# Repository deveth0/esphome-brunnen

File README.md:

# esphome-brunnen

Repository with all required stuff to build an esphome node that monitors the waterlevel and temperature of a well or cistern. It does not require any power connection as it's using a solar panel and some batteries. 

## PCB

You can find a KiCad Model in this repository. The PCB can be mounted (aka glued) to the battery case of the [Waveshare Solar Power Manager D](https://www.waveshare.com/solar-power-manager-d.htm). Using the spacers that come with the Solar board, you can mount it to the PCB. 

### Parts

| Number | Component | Position on PCB|
| --------- | ------ | -------- |
| 1 | Solar Panel, 6-24V, see below | | |
| 1 | [Waveshare Solar Power Manager D](https://www.waveshare.com/solar-power-manager-d.htm)|
| 3 | 18650 Li-ion batteries|
| 1 | MT3608 step up module | | |
| 1 | D1 Mini ESP32 with headers ||
| 1 | TL-136 Sensor, 4-20mA, 24V ||
| 1 | DS18B20 Sensor, waterproof ||
| 1 | JST-XH 2 Pin cable | |
| 2 | JST-XH 3 Pin cable | |
| 1 | JST-XH 4 Pin cable | |
| 1 | BC547 | Q1 |
| 1 | BC557 | Q2 |
| 1 | tantalum capacitor 35V  1uF | C1 |
| 1 | JST-XH 2 Pin Header | J3 |
| 2 | JST-XH 3 Pin Header | J1, J4 |
| 1 | JST-XH 4 Pin Header | J2 |
| 1 | DS18B20 Sensor, TO-92 package | U2 |
| 1 | Resistor, 4.7k | R1 |
| 1 | Resistor, 33k | R2 |
| 1 | Resistor, 100k | R3 |
| 2 | Resistor, 150k | R4, R5 (see note below) |
| 2 | Resistor, 1k | R6, R9 |
| 1 | Resistor, 150 | R7 |
| 1 | Resistor, 27k | R8 |
| 1 | Resistor, 10k | R10 |

### D1 Mini ESP32

Before adding the D1 Mini to your PCB (i highly recommend using headers), you need to install the software to the board. All subsequent updates can be done using OTA but the first installation requires an USB connection.

> [!CAUTION]
> DO NEVER CONNECT YOUR D1 BOARD VIA USB WHEN IT'S MOUNTED ON THE PCB

### Solar Panel

You can use any solar panel that provides between 6-24V. Choose wattage according to the placement of your panel. 

The resistors `R4` and `R5` are used to split the voltage of the solar panel into a range, that can be measured with an ESP32 gpio pin (max 3.3V). By using equally sized resistors, the voltage is cut by half, so this is fine for 6V panels.
Change the resistors to the following values, when using other panels, also change the multiply factor of the `solar_voltage` sensor in `brunnen.yaml`.

> [!WARNING]
> Some solar panels provide a slightly higher voltage than specified (e.g. 14V instead of 12V). To prevent any damage on the GPIO pin, use the resistor and multiply value of the next higher rated panel if you are not sure. This reduces the accuracy of the measured voltage a bit, but might save your D1.

| Panel | R4 | R5 | max V @ GPIO | `multiply` |
| ----- | -- | -- | ------|---------- |
| 6V | 150k | 150k| 3V |`multiply: 2`|
| 12V | 150k | 47k| 2.86|`multiply: 4.2`|
| 18V | 150k | 33k| 3.25V|`multiply: 5.5`|
| 24V | 150k | 22k| 3.07V |`multiply: 7.8`|

### MT3608 Step up Module

The pressure sensor requires 24V which are generated by a step up module. The module is disabled when the ESP32 is in deepsleep using a BC547 transistor to reduce the power consumption.

Before adding the MT3608 to your circuit, you need to measure and change the output voltage to 24V, use a multimeter for that task.

### Assembly

* Solder the 2 Pin JST-XH cable to your pressure sensor
* Solder one 3 Pin JST-XH cable to your waterproof DS18B20 sensor
* Solder one 1 Pin JST-XH cable to your MT3608 step-up
    * VIN
    * GND
    * VOUT
* Attach one 4 Pin JST-XH cable to your Waveshare Board:
    * GND
    * 5V
    * BAT+ (use the free terminal)
    * SOL+ (add cable together with solar panel to terminal)
* Add solar panel to Waveshare Board
* Attach batteries
* Solder all remaining parts to the PCB
* Check parts once again
* Connect J2 to JST-XH cable coming from Waveshare Board, your ESP32 should power up now
* Connect all remaining JST-XH cables
    * J1 - waterproof DS18B20
    * J3 - Pressure sensor
    * J4 - MT3608 Module

You should now see some sensor readings and can head over to the calibration of your pressure sensor. 

Note: to make the connections a bit more sturdy, you can also remove the terminals and solder all cables to the Waveshare Board

## Installation

### secrets.yaml

Create a `secrets.yaml` file which contains your WiFi-credentials:

```
wifi_ssid: "YOUR_SSID"
wifi_password: "YOUR_PASSWORD"
```

### Initial upload to ESP32

Attach your D1 Mini using USB to your computer, find out the correct COM port and run:

```
esphome run --device COM4 .\brunnen.yaml
```

The ESP32 should then reboot and connect to your wifi, note down it's IP.

> [!CAUTION]
> DO NEVER CONNECT YOUR D1 BOARD VIA USB WHEN IT'S MOUNTED TO THE PCB

### OTA Updates

When the initial upload is done, you can update your ESP32 using OTA updates. This does not require you to remove the board from the PCB. 

```
esphome run --device 10.0.50.132 .\brunnen.yaml
```

### D18B20 Sensors

Each of the D18B20 temperature sensors has a unique address that needs to be configured. Esphome logs all available devices when starting, you just need to figure out, which sensor is for the case and which one for water. 

```
[20:37:31][C][gpio.one_wire:020]: GPIO 1-wire bus:
[20:37:31][C][gpio.one_wire:021]:   Pin: GPIO5
[20:37:31][C][gpio.one_wire:080]:   Found devices:
[20:37:31][C][gpio.one_wire:082]:     0x5d4a131c35646128 (DS18B20)
[20:37:31][C][gpio.one_wire:082]:     0x8f00000e7dbdd128 (DS18B20)
```

### Pressure Sensor calibration

The pressure sensor gives around 4-20mA when submerged into water. Although this gives us a rough estimation, I recommend to calibrate the sensor with some known values. 

Use the log output to determine the values read by your ESP32, this is what we are looking for:

```
'Wasserstand Voltage': Sending state 0.27872 V with 2 decimals of accuracy
```

First note down the voltage when the sensor is not in water (basically 0cm). Then add as many data points as seem reasonable (e.g. one per meter).

When submerging the sensor, give it a minute or two so the value stabilizes.

Now update the mapping table to reflect your measurements
```
      - calibrate_linear:
            - 0.28 -> 0.0 # 0cm
            - 0.60 -> 1.2 # 120cm
            - 0.75 -> 2.2 # 220cm
            - 0.91 -> 3.2 # 320cm
            - 1.32 -> 4.2 # 420cm
```

## Home Assistant Integration 

Finally you can add the Board to your Home Assistant setup and configure a switch that enables/disables deep-sleep.

`Settings` > `Devices & Services` > `Add integration` > `esphome` > `Enter IP of your node`

### Deep Sleep Helper

By default the ESP32 board does not go to deep sleep. To allow OTA updates, a toggle in Home Assistant is used, that enables / disables sleep. As soon as the board wakes up, it checks if the toggle is enabled and only if so will sleep again. 

If you ever want to do an OTA update and your ESP32 is sleeping, disable the toggle, wait until it wakes up for the next time and you can proceed.

Create the toggle in Home Assistant:

`Settings` > `Devices & Services` > `Helpers` > `Create Helper` > `Toggle` 

Name the Helper `Enable ESPHome Deepsleep` (it's important that the id of the new helper matches the one configured in `brunnen.yaml`).

# Acknowledgement

* Thanks to [r0oland](https://github.com/r0oland) for the [ESP32 mini KiCad Library](https://github.com/r0oland/ESP32_mini_KiCad_Library)
* Thanks to [tathamoodie](https://github.com/tathamoddie) for his [blogpost]( https://tatham.blog/2021/02/06/esphome-batteries-deep-sleep-and-over-the-air-updates/) about deep sleep

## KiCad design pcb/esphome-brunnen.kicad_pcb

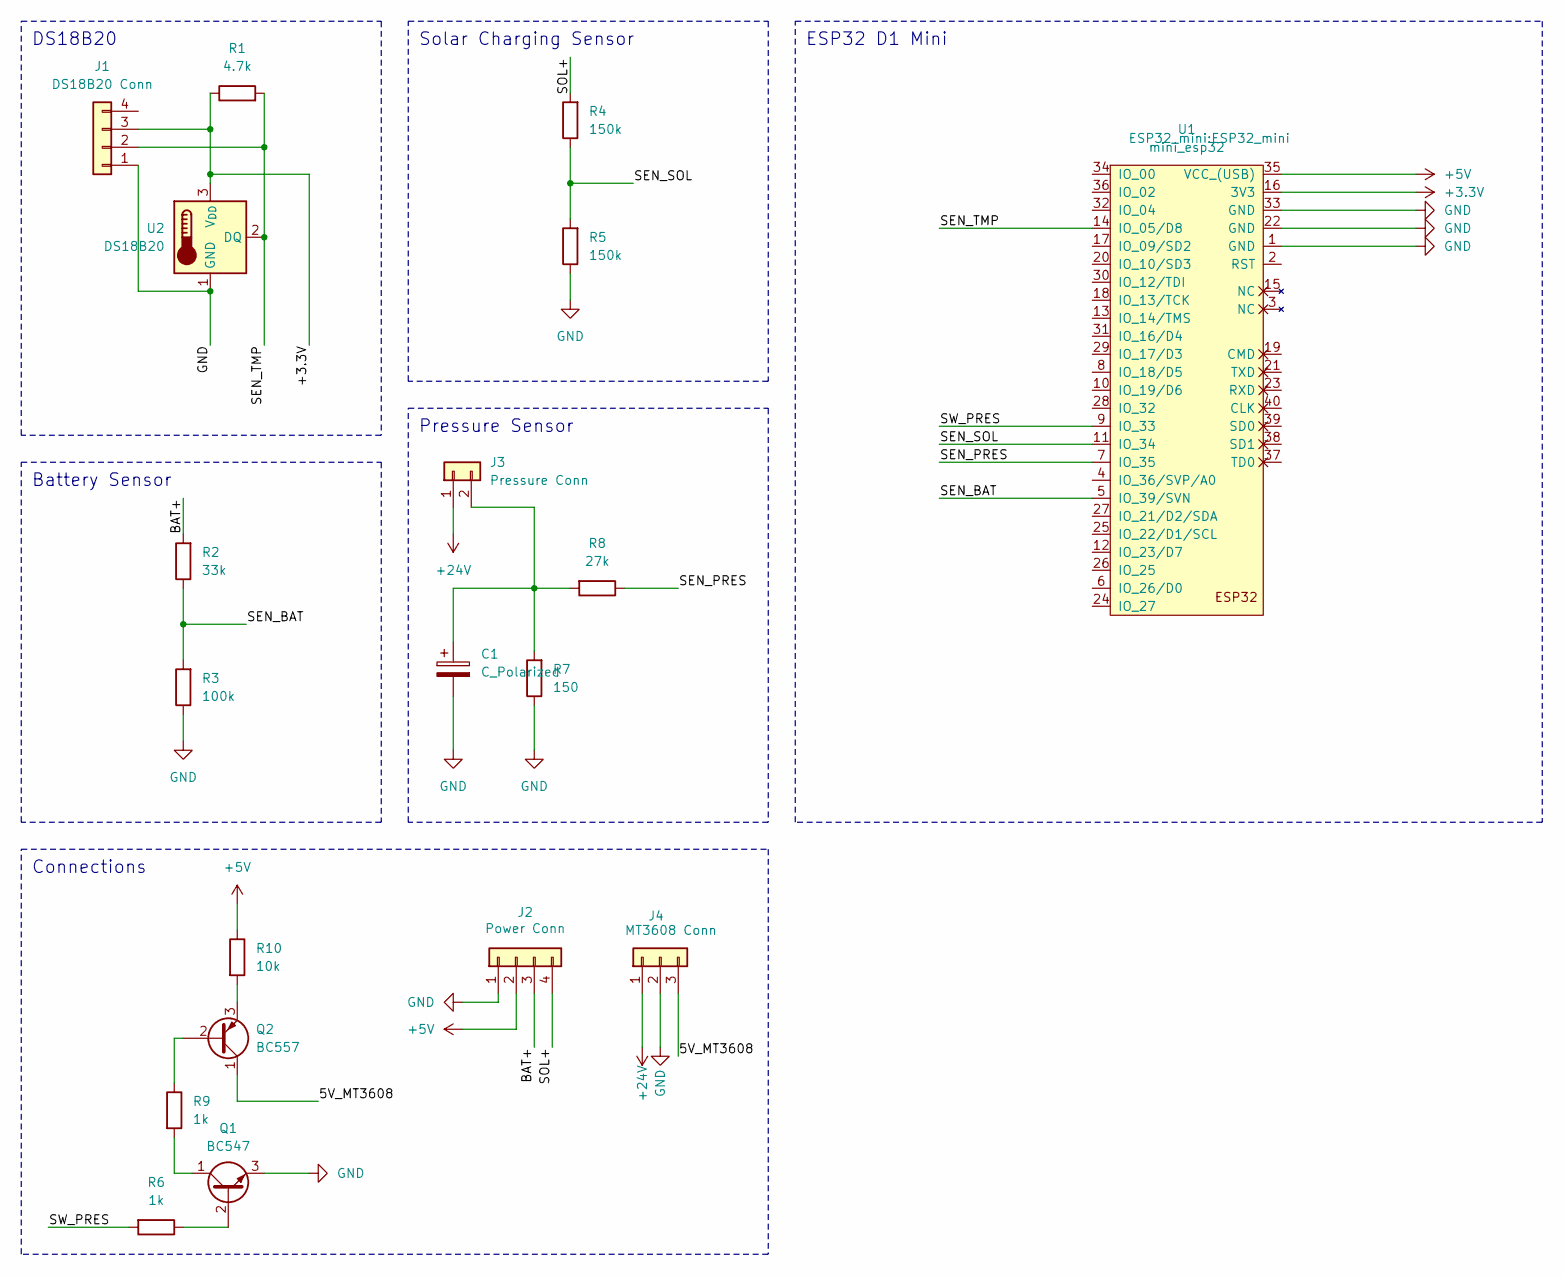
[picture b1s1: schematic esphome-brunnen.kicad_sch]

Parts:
C1: C_Polarized; CP_Radial_Tantal_D4.5mm_P2.50mm
J1: DS18B20 Conn; JST_XH_B3B-XH-A_1x03_P2.50mm_Vertical
J2: Power Conn; JST_XH_B4B-XH-A_1x04_P2.50mm_Vertical
J3: Pressure Conn; JST_XH_B2B-XH-A_1x02_P2.50mm_Vertical
J4: MT3608 Conn; JST_XH_B3B-XH-A_1x03_P2.50mm_Vertical
Q1: BC547; TO-92_Inline
Q2: BC557; TO-92_Inline
R1: 4.7k; R_Axial_DIN0207_L6.3mm_D2.5mm_P10.16mm_Horizontal
R2: 33k; R_Axial_DIN0207_L6.3mm_D2.5mm_P10.16mm_Horizontal
R3: 100k; R_Axial_DIN0207_L6.3mm_D2.5mm_P10.16mm_Horizontal
R4, R5: 150k; R_Axial_DIN0207_L6.3mm_D2.5mm_P10.16mm_Horizontal
R6, R9: 1k; R_Axial_DIN0207_L6.3mm_D2.5mm_P10.16mm_Horizontal
R7: 150; R_Axial_DIN0207_L6.3mm_D2.5mm_P10.16mm_Horizontal
R8: 27k; R_Axial_DIN0207_L6.3mm_D2.5mm_P10.16mm_Horizontal
R10: 10k; R_Axial_DIN0207_L6.3mm_D2.5mm_P10.16mm_Horizontal
U1: mini_esp32; ESP32_mini
U2: DS18B20; TO-92_Inline

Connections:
+3.3V: J1.3, R1.1, U1.16 (3V3), U2.3 (V_{DD})
+5V: J2.2, R10.1, U1.35 (VCC_(USB))
+24V: J3.1, J4.1
/5V_MT3608: J4.3, Q2.1 (C)
/BAT+: J2.3, R2.2
/SEN_BAT: R2.1, R3.2, U1.5 (IO_39/SVN)
/SEN_PRES: R8.1, U1.7 (IO_35)
/SEN_SOL: R4.1, R5.2, U1.11 (IO_34)
/SEN_TMP: J1.2, R1.2, U1.14 (IO_05/D8), U2.2 (DQ)
/SOL+: J2.4, R4.2
/SW_PRES: R6.2, U1.9 (IO_33)
GND: C1.2, J1.1, J2.1, J4.2, Q1.3 (E), R3.1, R5.1, R7.1, U1.1 (GND), U1.22 (GND), U1.33 (GND), U2.1 (GND)
unnamed: C1.1, J3.2, R7.2, R8.2
unnamed: Q1.2 (B), R6.1
unnamed: Q1.1 (C), R9.2
unnamed: Q2.2 (B), R9.1
unnamed: Q2.3 (E), R10.2

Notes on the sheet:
ESP32 D1 Mini
Connections
Pressure Sensor
Battery Sensor
DS18B20
Solar Charging Sensor

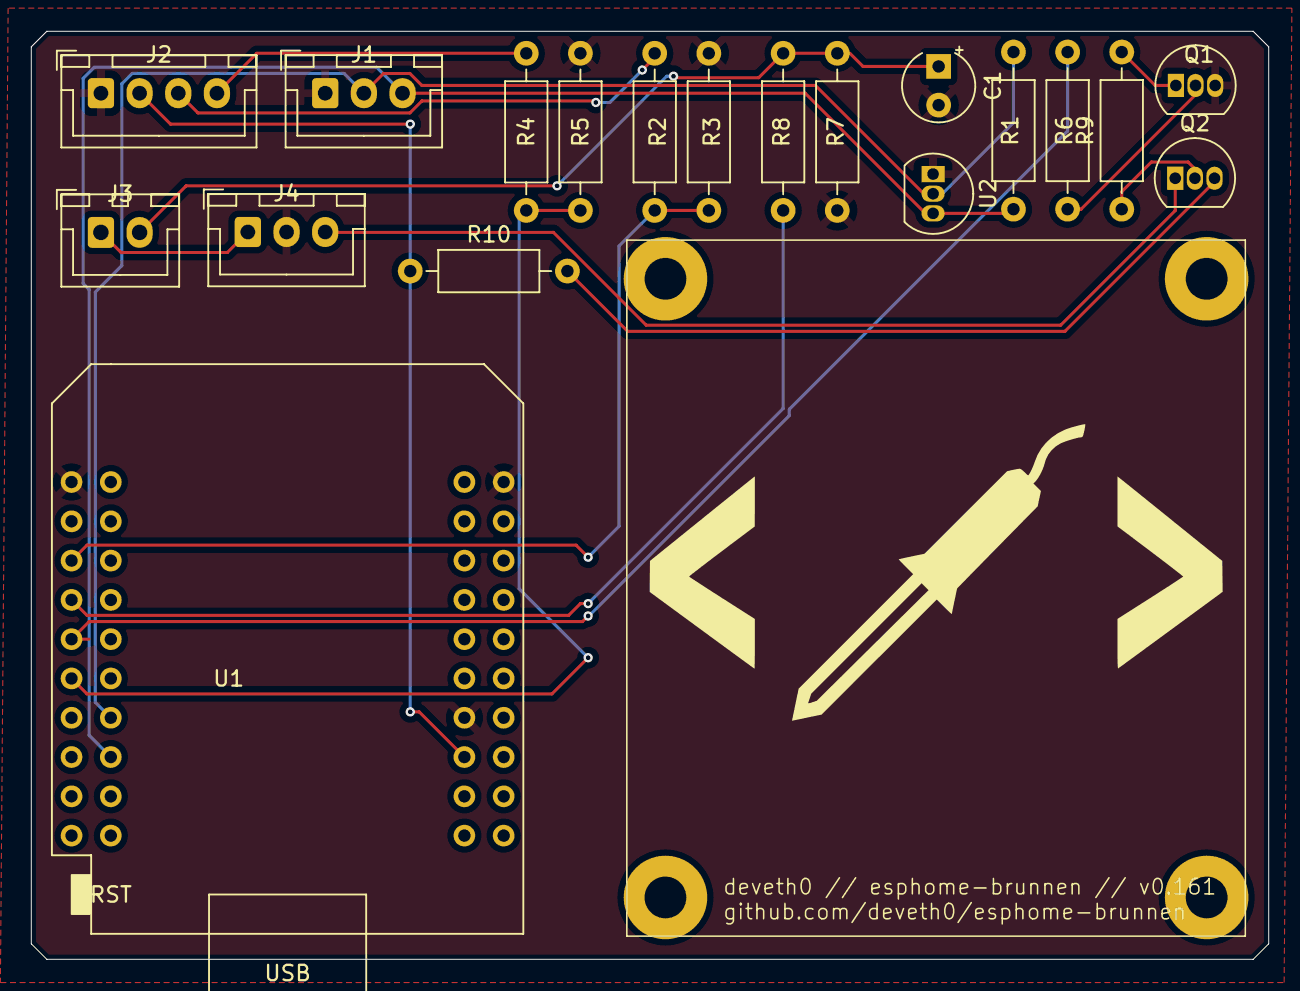
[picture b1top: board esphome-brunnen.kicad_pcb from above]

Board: 2 copper layers, 80.0 x 60.0 mm, 19 parts (0 on the bottom side), 17 nets.

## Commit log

2024-10-06 Calibration, deepsleep
2024-10-11 Update and PCB
2024-10-21 Set 100% battery to 4V
2025-04-01 Update with calibration values
